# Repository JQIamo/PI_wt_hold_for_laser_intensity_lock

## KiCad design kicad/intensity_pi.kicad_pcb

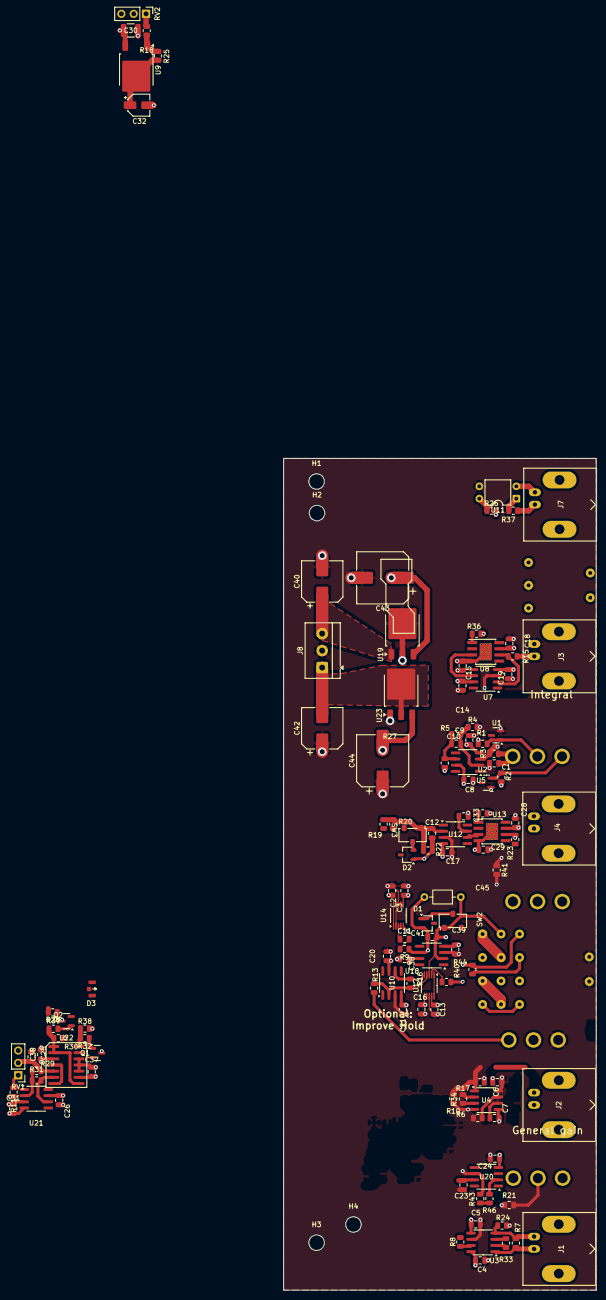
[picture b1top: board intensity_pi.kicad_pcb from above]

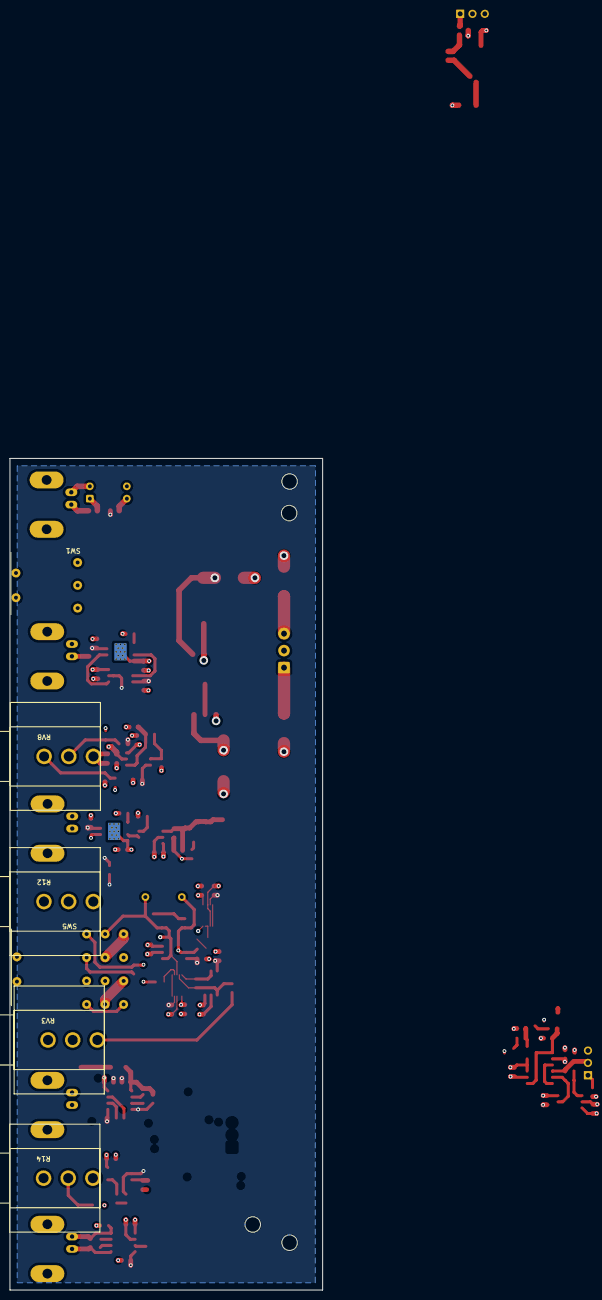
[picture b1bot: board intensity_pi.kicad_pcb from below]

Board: 4 copper layers, 64.4 x 171.2 mm, 128 parts (6 on the bottom side), 69 nets.

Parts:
C1, C4, C5, C6, C7, C8, C9, C10, C14, C15, C17, C18, C19, C20, C21, C23, C24, C25, C26, C28, C29, C31, C33, C36, C37, C38, C39: 100nF; C_0805_2012Metric
C2, C3, C13, C16: 1uF; C_0805_2012Metric
C11: C; C_0805_2012Metric
C12: 100p; C_0805_2012Metric
C30: 10uF; C_1210_3225Metric
C32: 22uF; CP_Elec_4x5.8
C40, C42: 100uF; CP_Elec_8x6.5
C41: 10nF; C_0805_2012Metric
C43, C44: 220uF; CP_Elec_10x10.5
C45: C; C_Axial_L3.8mm_D2.6mm_P7.50mm_Horizontal
D1, D2: D; TSOT-23
D3: LED_Dual_KKA; GR LED
H1, H2, H3, H4: MountingHole; MountingHole_3.2mm_M3_ISO14580
J1: Input A; BNC_Amphenol_B6252HB-NPP3G-50_Horizontal
J2: Input B / Setpoint; BNC_Amphenol_B6252HB-NPP3G-50_Horizontal
J3: Monitor; BNC_Amphenol_B6252HB-NPP3G-50_Horizontal
J4: Output; BNC_Amphenol_B6252HB-NPP3G-50_Horizontal
J7: select 1; BNC_Amphenol_B6252HB-NPP3G-50_Horizontal
J8: Screw_Terminal_01x03; TerminalBlock_4Ucon_1x03_P3.50mm_Horizontal
Q1, Q2: 2N7002E; SOT-23
R1, R2, R3, R4, R5, R6, R7, R8, R10, R19, R20, R22, R27, R29, R30, R31, R38, R40: 10k; R_0805_2012Metric
R9, R17, R18, R21, R24, R26, R28, R41: 1k; R_0805_2012Metric
R11, R16: 100k; R_0805_2012Metric
R12: 100k; Bourns Circular Pots
R13: 5k; R_0805_2012Metric
R14: 10k; Bourns Circular Pots
R15, R23: 50; R_0805_2012Metric
R25: 330; R_0805_2012Metric
R32, R39: 100; R_0805_2012Metric
R33, R34: DNP; R_0805_2012Metric
R35, R36: 3.3k; R_0805_2012Metric
R37: 180; R_0805_2012Metric
R43, R46: 11k; R_0805_2012Metric
R44: 1M; R_0805_2012Metric
RV1: 100k; PinHeader_1x03_P2.54mm_Vertical
RV2: 2k; PinHeader_1x03_P2.54mm_Vertical
RV3: 5k; Bourns Circular Pots
RV8: 100k; Bourns Circular Pots
SW1: SW_SPDT; Right Angle SPDT Switch
SW2, SW3: SW_SPDT; TDD DIP Switch
SW5: EG6100-ND; Right Angle 3PDT Switch
U1, U2: LM4040DBZ-5; SOT-23
U3, U4: INA849; SOIC-8_3.9x4.9mm_P1.27mm
U5, U7, U10, U12, U18, U20, U21: OPA189; SOIC-8_3.9x4.9mm_P1.27mm
U8, U13: BUF634A; TI_SO-PowerPAD-8_ThermalVias
U9: LM317_TO-252; TO-252-2
U11: PC817; DIP-4_W7.62mm
U14, U17: TMUX6123; VSSOP-10_3x3mm_P0.5mm
U19: L7815; TO-252-3_TabPin2
U22: 4x Comparator; SOIC-14
U23: L7915; TO-252-3_TabPin2

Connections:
+15V: C2.1, C4.1, C6.1, C8.1, C13.1, C14.1, C18.1, C20.1, C23.1, C26.1, C28.1, C30.1, C36.1, C38.1, C43.1, R1.2, R11.2, R26.1, R28.1, R30.2, R38.2, U3.8 (Vs+), U4.8 (Vs+), U5.7 (V+), U7.7 (V+), U8.7 (V+), U9.3 (VI), U10.7 (V+), U13.7 (V+), U14.9 (VDD), U17.9 (VDD), U18.7 (V+), U19.3 (OUT), U20.7 (V+), U21.7 (V+), U22.3 (V+)
+V_DC_unregulated: C40.1, J8.3, U19.1 (IN)
-15V: C3.2, C5.2, C7.2, C9.2, C15.2, C16.2, C17.2, C19.2, C21.2, C24.2, C29.2, C31.2, C37.2, C39.2, C44.2, R2.1, R35.1, R36.1, U3.5 (Vs-), U4.5 (Vs-), U5.4 (V-), U7.4 (V-), U8.4 (V-), U8.9 (EP), U10.4 (V-), U12.4 (V-), U13.4 (V-), U13.9 (EP), U14.6 (VSS), U17.6 (VSS), U18.4 (V-), U20.4 (V-), U21.4 (V-), U22.10 (-), U22.11 (+), U22.12 (V-), U23.3 (VO)
-V_DC_unregulated: C42.2, J8.1, U23.2 (VI)
Error_signal: R12.1, R41.2, R43.2, RV3.1, U20.6, U22.4 (-), U22.7 (+)
GND: C1.1, C2.2, C3.1, C4.2, C5.1, C6.2, C7.1, C8.2, C9.1, C13.2, C14.2, C15.1, C16.1, C17.1, C18.2, C19.1, C20.2, C21.1, C23.2, C24.1, C25.1, C26.2, C28.2, C29.1, C30.2, C31.1, C32.2, C33.2, C36.2, C37.1, C38.2, C39.1, C40.2, C42.1, C43.2, C44.1, J3.2 (Ext), J4.2 (Ext), J8.2, Q1.3 (D), Q2.3 (D), R4.1, R17.1, R21.1, R24.1, RV1.3, RV2.2, RV2.3, RV3.3, SW1.2 (B), SW5.13, U1.2 (A), U2.1 (K), U3.6 (Ref), U4.6 (Ref), U10.3 (+), U11.3, U12.3 (+), U14.2, U14.8 (GND), U17.8 (GND), U18.3 (+), U19.2 (GND), U21.3 (+), U22.9 (+), U23.1 (GND)
Input_A: R8.1, U3.7
Input_B: R6.1, U4.7
Internal_setpoint: C10.1, R5.2, R27.1, U5.6
unnamed: C1.2, R3.1, RV8.2
unnamed: C11.1, U14.3, U14.4
unnamed: C11.2, R9.2
unnamed: C41.1, C45.2, D1.2 (A), R9.1, R19.1, R44.2, SW5.1, U18.6
unnamed: D1.1 (K), SW2.2 (B)
unnamed: D2.2 (A), SW3.2 (B)
unnamed: C12.1, D2.1 (K), R22.2, R23.1, U13.6 (OUT)
unnamed: D3.3 (A), SW5.10, SW5.12
unnamed: D3.1 (K1), Q1.2 (S)
unnamed: D3.2 (K2), Q2.2 (S)
unnamed: J1.2 (Ext), R7.1, R24.2, U3.4 (+)
unnamed: J1.1 (In), R7.2, U3.1 (-)
unnamed: J2.2 (Ext), R10.1, R17.2, U4.1 (-)
unnamed: J2.1 (In), R10.2, U4.4 (+)
unnamed: J3.1 (In), R15.2
unnamed: J4.1 (In), R23.2
unnamed: J7.2 (Ext), U11.2
unnamed: J7.1 (In), R37.2
unnamed: Q1.1 (G), R32.1
unnamed: Q2.1 (G), R39.2
unnamed: R11.1, RV1.1
unnamed: R12.2, R40.1
unnamed: R13.1, RV3.2
unnamed: R14.1, R21.2
unnamed: R16.2, R20.1, U10.6, U17.5
unnamed: R18.1, RV2.1
unnamed: R28.2, SW5.8
unnamed: R32.2, R38.1, U22.14
unnamed: R33.1, U3.3 (Rg)
unnamed: R33.2, U3.2 (Rg)
unnamed: R34.1, U4.3 (Rg)
unnamed: R34.2, U4.2 (Rg)
unnamed: R37.1, U11.1
unnamed: R40.2, U17.2
unnamed: R43.1, R46.2
unnamed: R44.1, SW5.4
unnamed: R3.2, SW1.1 (A), U5.3 (+)
unnamed: C41.2, C45.1, SW2.1 (A), SW5.2, U14.5, U17.3, U18.2 (-)
unnamed: C12.2, R19.2, R20.2, R22.1, SW3.1 (A), U12.2 (-)
unnamed: SW5.3, SW5.5
unnamed: SW5.9, SW5.11
unnamed: R1.1, RV8.1, U1.1 (K)
unnamed: R2.2, RV8.3, U2.2 (A)
unnamed: C10.2, R4.2, R5.1, U5.2 (-)
unnamed: R41.1, U7.3 (+)
unnamed: R15.1, U7.2 (-), U8.6 (OUT)
unnamed: R36.2, U8.1 (BW)
unnamed: U7.6, U8.3 (IN)
unnamed: R18.2, R25.1, U9.1 (ADJ)
unnamed: R13.2, R16.1, U10.2 (-), U17.4
unnamed: R35.2, U13.1 (BW)
unnamed: U12.6, U13.3 (IN)
unnamed: R26.2, U11.4, U14.1 (SEL1), U14.10 (SEL2), U17.1 (SEL1), U17.10 (SEL2)
unnamed: R6.2, R8.2, R27.2, U20.3 (+)
unnamed: R14.2, R46.1, U20.2 (-)
unnamed: R29.2, R31.1, U21.2 (-)
unnamed: C25.2, R29.1, RV1.2, U22.5 (+)
unnamed: R31.2, U21.6, U22.6 (-)
unnamed: R30.1, R39.1, U22.1, U22.2, U22.8 (-)
Vlim+: C32.1, C33.1, R25.2, U9.2 (VO), U12.7 (V+)

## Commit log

2025-07-19 different way to route design
